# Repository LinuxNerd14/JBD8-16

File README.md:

# The JBD8-16

A computer with the skeleton of the BE6502 by the revered [Ben Eater](https://eater.net/) with the ultimate goal of running DOOM and making a decent platform for programing in asembly or C at a very fundemental level.

    This computer is currently still deep in hardware development but has a diverse set of planned features like hardware based random numbers and way more RAM than what is reasonable along with an implimentation of the VERA by the [8BitGuy](https://www.the8bitguy.com/).

This is by far not a finished project as these features awaiting implimentation:

1. Memory bank
2. Proper random number generator
3. Micro SD card
4. Better display or VGA output
5. Easily reproducable PCB's

List of contributers:

1. [Brian Dean Ullery](https://github.com/NonzeroCornet)

2. [Joshua Lin Yuan]([LinuxNerd14 (Joshua Yuan) · GitHub](https://github.com/LinuxNerd14))

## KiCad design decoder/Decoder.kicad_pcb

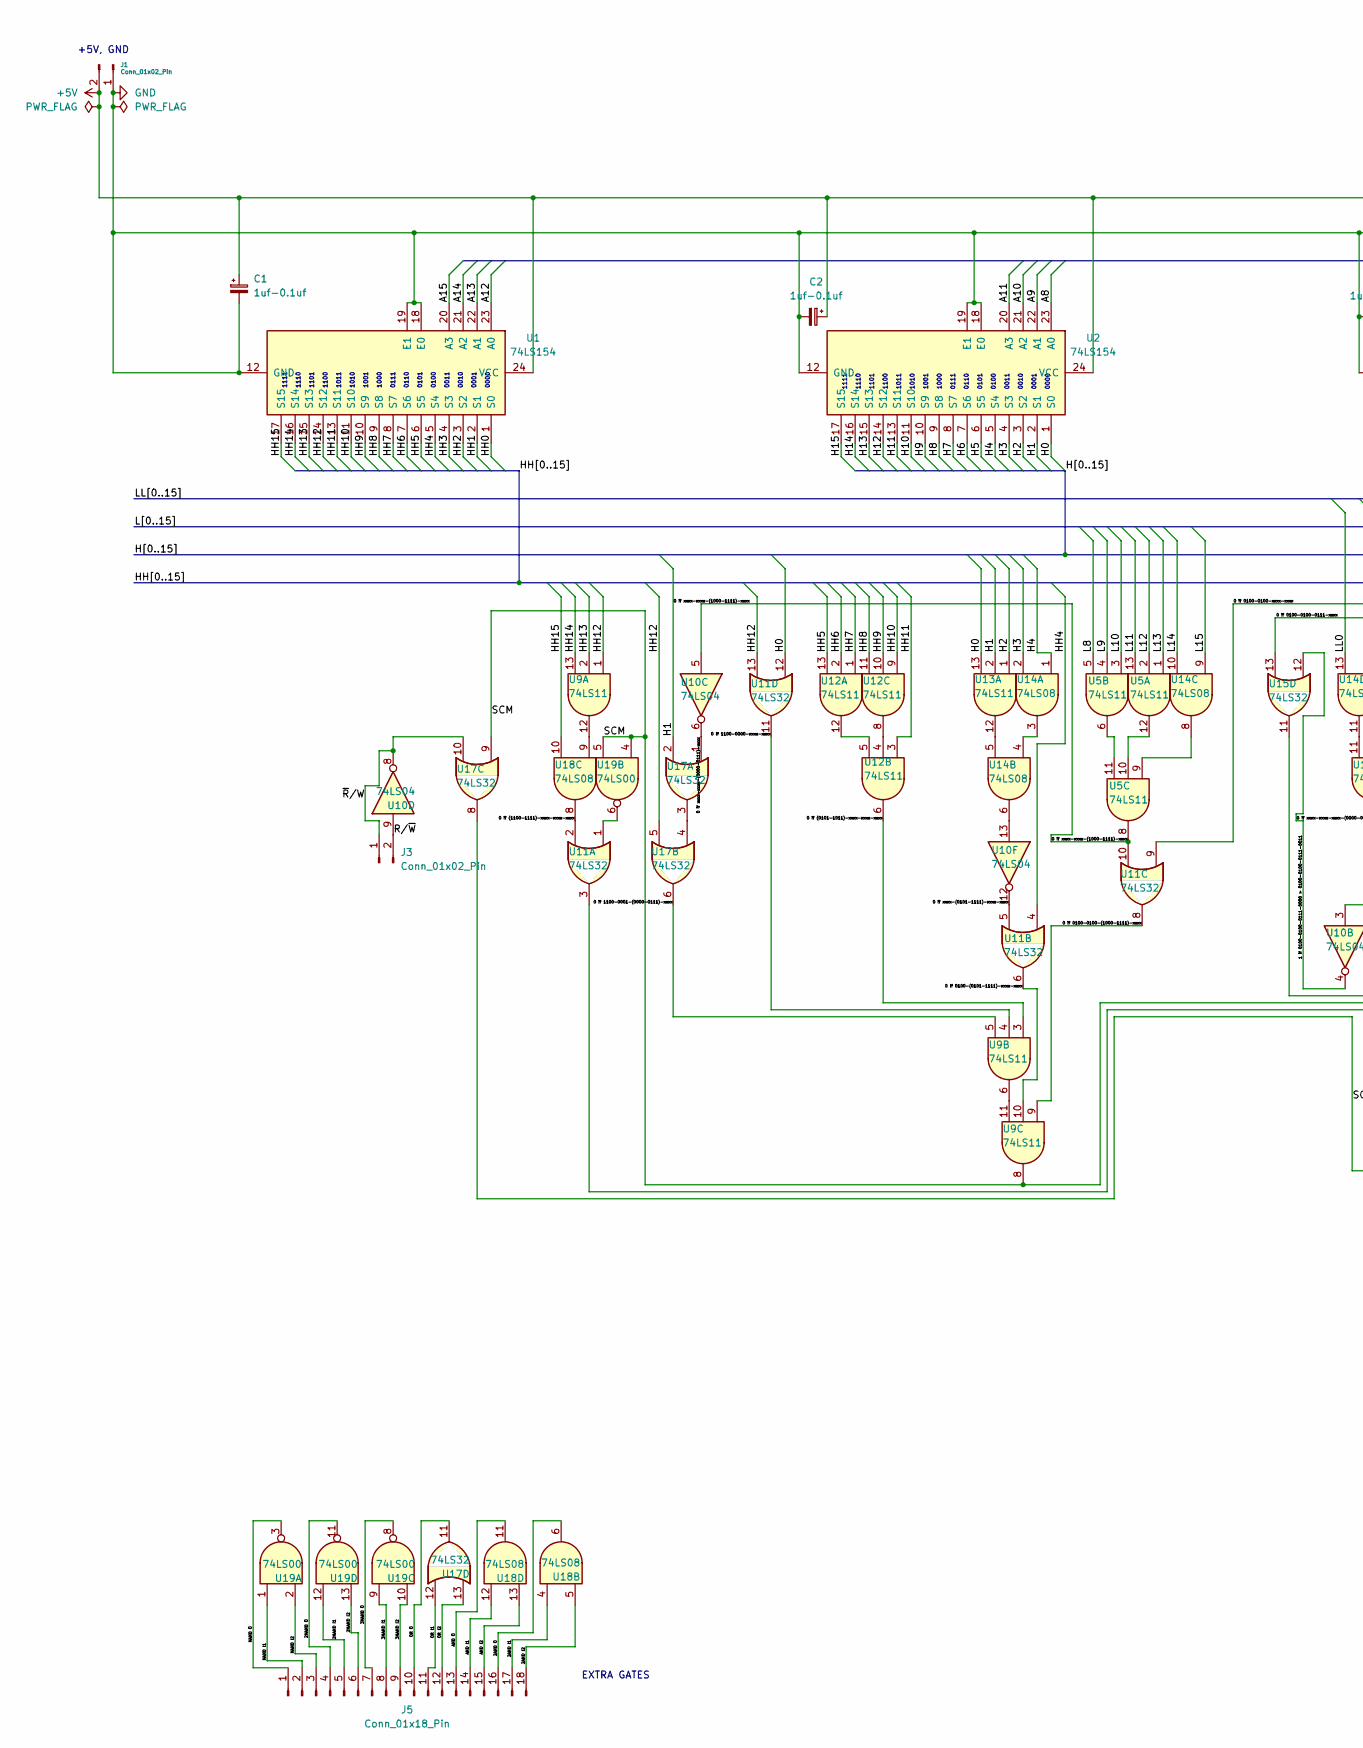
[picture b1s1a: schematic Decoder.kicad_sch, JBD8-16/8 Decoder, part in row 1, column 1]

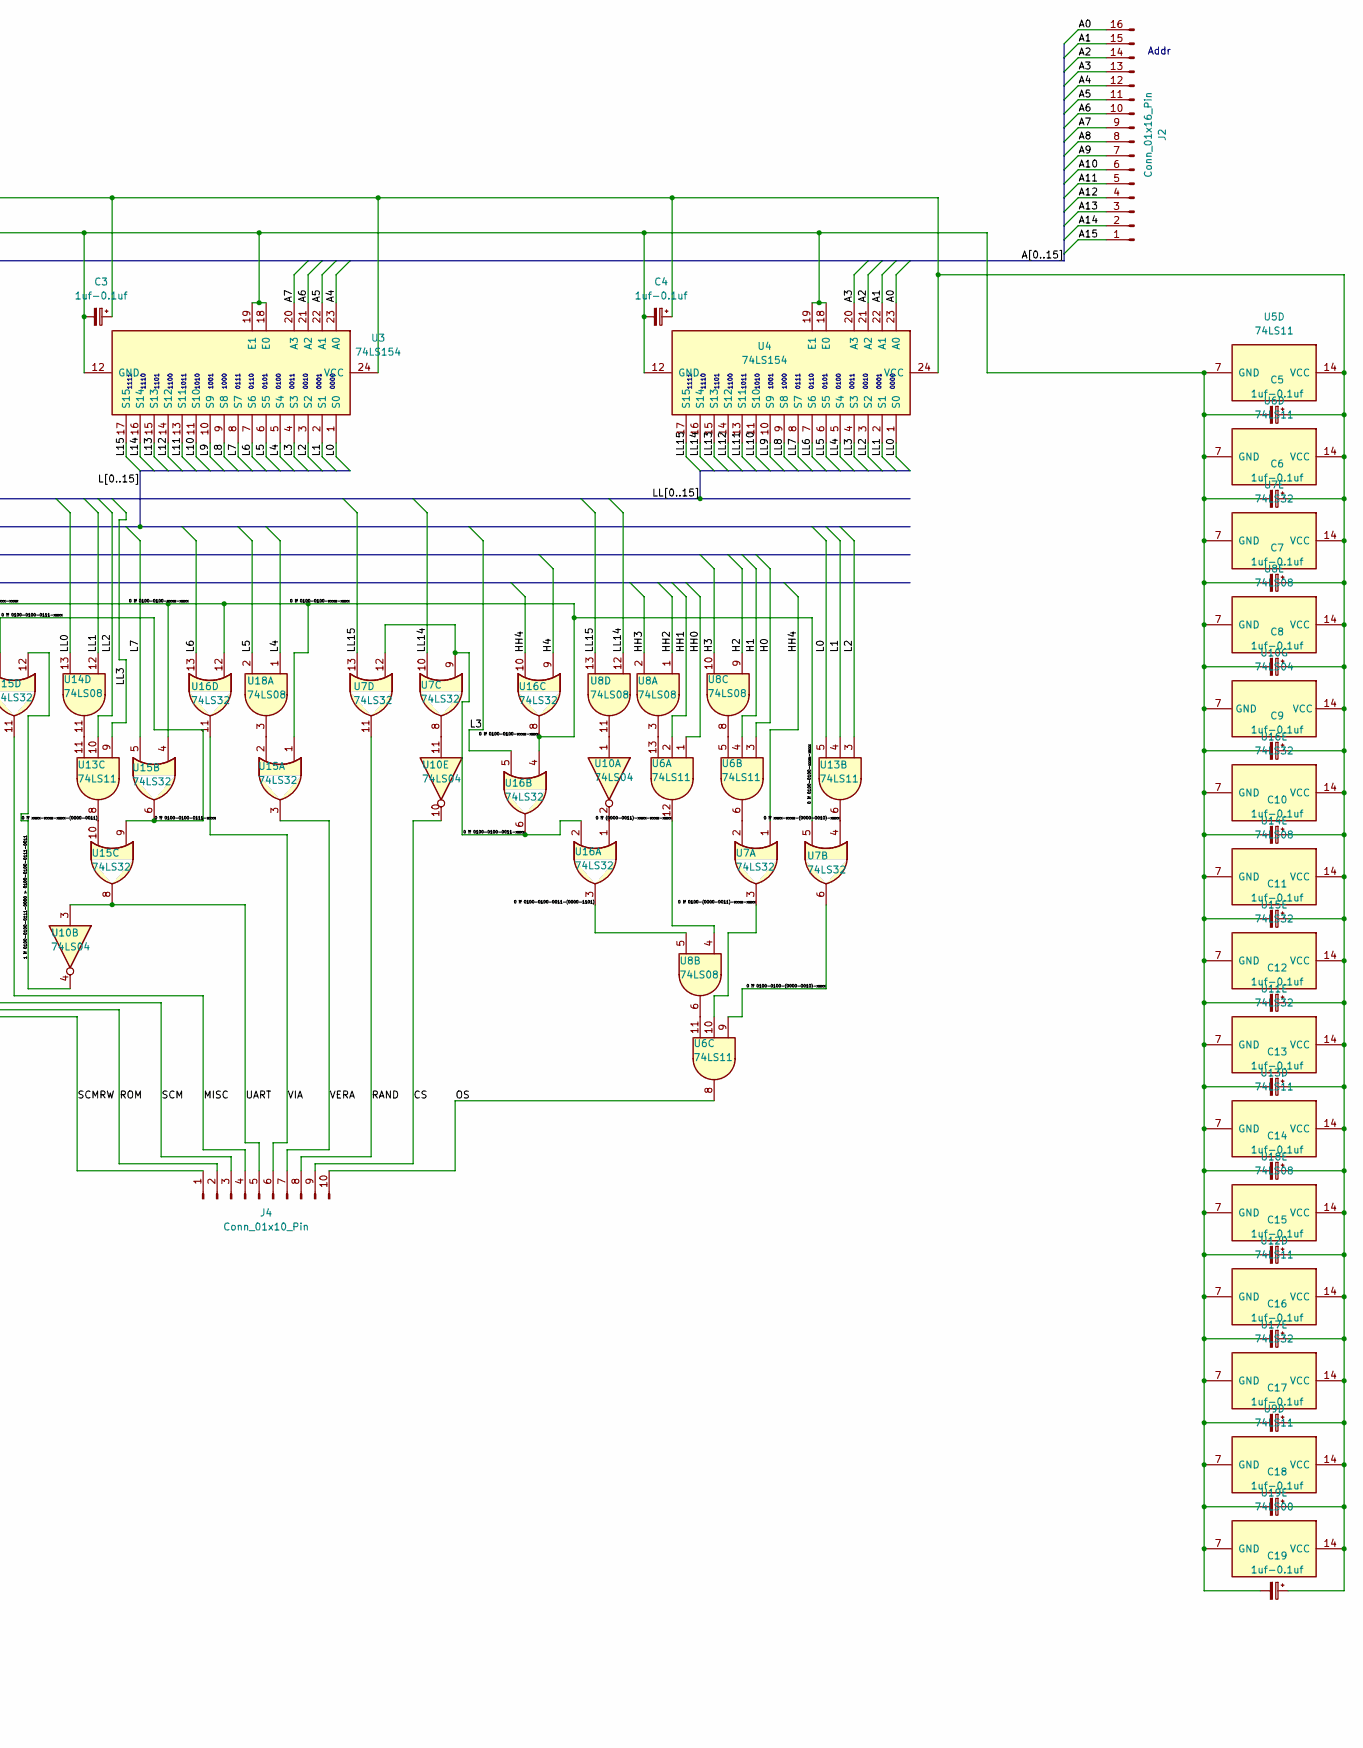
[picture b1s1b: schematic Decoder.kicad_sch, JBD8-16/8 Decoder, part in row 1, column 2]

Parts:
C1, C2, C3, C4, C5, C6, C7, C8, C9, C10, C11, C12, C13, C14, C15, C16, C17, C18, C19: 1uf-0.1uf; CP_Radial_Tantal_D5.0mm_P2.50mm
J1, J3: Conn_01x02_Pin; PinHeader_1x02_P2.54mm_Vertical
J2: Conn_01x16_Pin; PinHeader_1x16_P2.54mm_Vertical
J4: Conn_01x10_Pin; PinHeader_1x10_P2.54mm_Vertical
J5: Conn_01x18_Pin; PinHeader_1x18_P2.54mm_Vertical
U1, U2, U3, U4: 74LS154; DIP-24_W7.62mm_Socket
U5, U6, U9, U12, U13: 74LS11; DIP-14_W7.62mm_Socket
U7, U11, U15, U16, U17: 74LS32; DIP-14_W7.62mm_Socket
U8, U14, U18: 74LS08; DIP-14_W7.62mm_Socket
U10: 74LS04; DIP-14_W7.62mm_Socket
U19: 74LS00; DIP-14_W7.62mm_Socket

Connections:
+5V: C1.1, C2.1, C3.1, C4.1, C5.1, C6.1, C7.1, C8.1, C9.1, C10.1, C11.1, C12.1, C13.1, C14.1, C15.1, C16.1, C17.1, C18.1, C19.1, J1.2, U1.24 (VCC), U2.24 (VCC), U3.24 (VCC), U4.24 (VCC), U5.14 (VCC), U6.14 (VCC), U7.14 (VCC), U8.14 (VCC), U9.14 (VCC), U10.14 (VCC), U11.14 (VCC), U12.14 (VCC), U13.14 (VCC), U14.14 (VCC), U15.14 (VCC), U16.14 (VCC), U17.14 (VCC), U18.14 (VCC), U19.14 (VCC)
/0 if 0100-0100-0011-(0000-1101): U8.5, U16.3
/0 if 0100-0100-0011-xxxx: U7.9, U7.12, U16.2, U16.6
/0 if 0100-0100-0111-xxxx: U15.6, U15.9, U15.13
/0 if 0100-0100-(0000-0010)-xxxx: U6.9, U7.6
/0 if 0100-0100-(1000-1111)-xxxx: U9.9, U11.8
/0 if 0100-0100-xxxx-xxxx: U7.5, U11.9, U15.1, U15.4, U16.4, U16.8, U16.12
/0 if 0100-(0000-0011)-xxxx-xxxx: U6.10, U7.3
/0 if 0100-(0101-1111)-xxxx-xxxx: U9.10, U11.6
/0 if 1100-0000-xxxx-xxxx: U9.4, U11.11
/0 if 1100-0001-(0000-0111)-xxxx: U9.5, U17.6
/0 if (0000-0011)-xxxx-xxxx-xxxx: U6.12, U8.4
/0 if (0101-1011)-xxxx-xxxx-xxxx: U9.3, U12.6
/0 if (1100-1111)-xxxx-xxxx-xxxx: U11.2, U18.8
/0 if xxxx-(0101-1111)-xxxx-xxxx: U10.12, U11.5
/0 if xxxx-xxxx-(0000-0010)-xxxx: U7.4, U13.6
/0 if xxxx-xxxx-(0000-0111)-xxxx: U10.6, U17.1
/0 if xxxx-xxxx-(1000-1111)-xxxx: U5.8, U10.5, U11.10
/0 if xxxx-xxxx-xxxx-(0000-0011): U13.8, U15.10
/1 if 0100-0100-0111-0000 > 0100-0100-0111-0011: U10.4, U15.12
/2AND I1: J5.17, U18.4
/2AND I2: J5.18, U18.5
/2AND O: J5.16, U18.6
/2NAND I1: J5.5, U19.12
/2NAND I2: J5.6, U19.13
/2NAND O: J5.4, U19.11
/3NAND I1: J5.8, U19.9
/3NAND I2: J5.9, U19.10
/3NAND O: J5.7, U19.8
/A0: J2.16, U4.23 (A0)
/A1: J2.15, U4.22 (A1)
/A2: J2.14, U4.21 (A2)
/A3: J2.13, U4.20 (A3)
/A4: J2.12, U3.23 (A0)
/A5: J2.11, U3.22 (A1)
/A6: J2.10, U3.21 (A2)
/A7: J2.9, U3.20 (A3)
/A8: J2.8, U2.23 (A0)
/A9: J2.7, U2.22 (A1)
/A10: J2.6, U2.21 (A2)
/A11: J2.5, U2.20 (A3)
/A12: J2.4, U1.23 (A0)
/A13: J2.3, U1.22 (A1)
/A14: J2.2, U1.21 (A2)
/A15: J2.1, U1.20 (A3)
/AND I1: J5.14, U18.12
/AND I2: J5.15, U18.13
/AND O: J5.13, U18.11
/CS: J4.9, U10.10
/H0: U2.1 (S0), U6.3, U11.12, U13.13
/H1: U2.2 (S1), U6.4, U13.2, U17.2
/H2: U2.3 (S2), U8.9, U13.1
/H3: U2.4 (S3), U8.10, U14.2
/H4: U2.5 (S4), U14.1, U16.9
/H5: U2.6 (S5)
/H6: U2.7 (S6)
/H7: U2.8 (S7)
/H8: U2.9 (S8)
/H9: U2.10 (S9)
/H10: U2.11 (S10)
/H11: U2.13 (S11)
/H12: U2.14 (S12)
/H13: U2.15 (S13)
/H14: U2.16 (S14)
/H15: U2.17 (S15)
/HH0: U1.1 (S0), U6.1
/HH1: U1.2 (S1), U6.2
/HH2: U1.3 (S2), U8.1
/HH3: U1.4 (S3), U8.2
/HH4: U1.5 (S4), U7.1, U11.4, U16.10
/HH5: U1.6 (S5), U12.13
/HH6: U1.7 (S6), U12.2
/HH7: U1.8 (S7), U12.1
/HH8: U1.9 (S8), U12.11
/HH9: U1.10 (S9), U12.10
/HH10: U1.11 (S10), U12.9
/HH11: U1.13 (S11), U12.3
/HH12: U1.14 (S12), U9.1, U11.13, U17.5
/HH13: U1.15 (S13), U9.2
/HH14: U1.16 (S14), U9.13
/HH15: U1.17 (S15), U18.10
/L0: U3.1 (S0), U13.5
/L1: U3.2 (S1), U13.4
/L2: U3.3 (S2), U13.3
/L3: U3.4 (S3), U16.5
/L4: U3.5 (S4), U18.1
/L5: U3.6 (S5), U18.2
/L6: U3.7 (S6), U16.13
/L7: U3.8 (S7), U15.5
/L8: U3.9 (S8), U5.5
/L9: U3.10 (S9), U5.4
/L10: U3.11 (S10), U5.3
/L11: U3.13 (S11), U5.13
/L12: U3.14 (S12), U5.2
/L13: U3.15 (S13), U5.1
/L14: U3.16 (S14), U14.10
/L15: U3.17 (S15), U14.9
/LL0: U4.1 (S0), U14.13
/LL1: U4.2 (S1), U14.12
/LL2: U4.3 (S2), U13.10
/LL3: U4.4 (S3), U13.9
/LL4: U4.5 (S4)
/LL5: U4.6 (S5)
/LL6: U4.7 (S6)
/LL7: U4.8 (S7)
/LL8: U4.9 (S8)
/LL9: U4.10 (S9)
/LL10: U4.11 (S10)
/LL11: U4.13 (S11)
/LL12: U4.14 (S12)
/LL13: U4.15 (S13)
/LL14: U4.16 (S14), U7.10, U8.12
/LL15: U4.17 (S15), U7.13, U8.13
/MISC: J4.4, U15.11
/NAND I1: J5.2, U19.1
/NAND I2: J5.3, U19.2
/NAND O: J5.1, U19.3
/OR I1: J5.11, U17.12
/OR I2: J5.12, U17.13
/OR O: J5.10, U17.11
/OS: J4.10, U6.8
/RAND: J4.8, U7.11
/ROM: J4.2, U11.3
/R/~W: J3.2, U10.9
/SCM: J4.3, U9.8, U17.9, U19.4, U19.5
/SCMRW: J4.1, U17.8
/UART: J4.5, U10.3, U15.8
/VERA: J4.7, U15.3
/VIA: J4.6, U16.11
/~R/W: J3.1, U10.8, U17.10
GND: C1.2, C2.2, C3.2, C4.2, C5.2, C6.2, C7.2, C8.2, C9.2, C10.2, C11.2, C12.2, C13.2, C14.2, C15.2, C16.2, C17.2, C18.2, C19.2, J1.1, U1.12 (GND), U1.18 (E0), U1.19 (E1), U2.12 (GND), U2.18 (E0), U2.19 (E1), U3.12 (GND), U3.18 (E0), U3.19 (E1), U4.12 (GND), U4.18 (E0), U4.19 (E1), U5.7 (GND), U6.7 (GND), U7.7 (GND), U8.7 (GND), U9.7 (GND), U10.7 (GND), U11.7 (GND), U12.7 (GND), U13.7 (GND), U14.7 (GND), U15.7 (GND), U16.7 (GND), U17.7 (GND), U18.7 (GND), U19.7 (GND)
unnamed: U5.10, U5.12
unnamed: U5.6, U5.11
unnamed: U6.5, U8.8
unnamed: U6.6, U7.2
unnamed: U6.11, U8.6
unnamed: U6.13, U8.3
unnamed: U9.6, U9.11
unnamed: U8.11, U10.1
unnamed: U10.2, U16.1
unnamed: U7.8, U10.11
unnamed: U10.13, U14.6
unnamed: U11.1, U19.6
unnamed: U12.4, U12.8
unnamed: U12.5, U12.12
unnamed: U13.11, U14.11
unnamed: U13.12, U14.5
unnamed: U14.3, U14.4
unnamed: U5.9, U14.8
unnamed: U15.2, U18.3
unnamed: U17.3, U17.4
unnamed: U9.12, U18.9

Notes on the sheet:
Addr
EXTRA GATES
1111 1110 1101 1100 1011 1010 1001 1000 0111 0110 0101 0100 0011 0010 0001 0000
+5V, GND

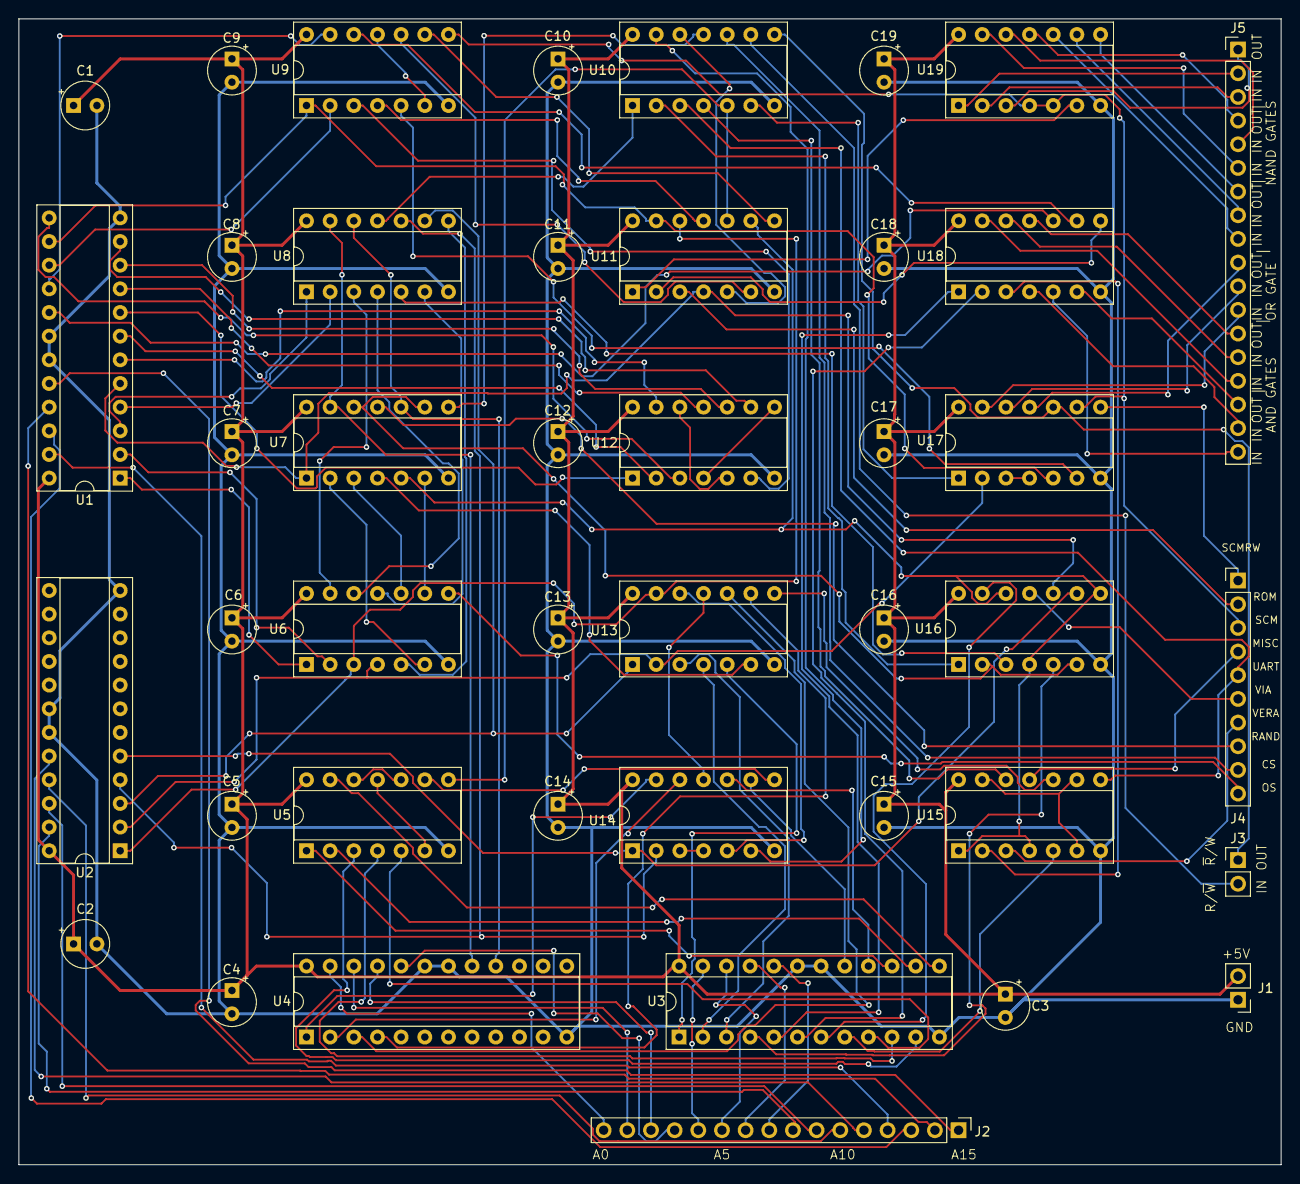
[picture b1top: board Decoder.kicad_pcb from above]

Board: 2 copper layers, 135.5 x 123.0 mm, 43 parts (0 on the bottom side), 131 nets.

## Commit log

2024-10-26 JBD8-16
2024-10-27 worked on SCM
2024-10-28 Better README
2024-11-03 Worked on SCM and README FIX THE GAP IN THE SCM BETWEEN 0000-0110-0001-0000 and 0001-0000-0000-0000
2024-11-03 Finished SCM and made the chematic paper larger
2024-11-04 Worked on OS mem space, adding of 4th decoder needed
2024-11-05 added and image to the README
2024-11-06 Almost done with OS mem and reduced the complexity of many sectors uisng another decoder
2024-11-06 Worked on OS mem
2024-11-06 almost done with ROM and SHM map
2024-11-07 FINISHED MEMORY LOGICgit add .git add .!
2024-11-07 Worked on the BANK
2024-11-08 worked on mem bank
2024-11-08 Made the Mem Bank work properly
2024-11-08 worked on the CS on some chips
2024-11-16 New memory map, New logic, Added VIA, Hooked up a screen and UART, Better memory map table
2024-11-16 updated READMER
2024-11-16 Fixed untracked symbols
2024-11-16 Fixed even more untracked parts
2024-11-23 Fixed unconnected VCC on U24
2024-11-24 general fixes to decoder
2024-11-27 Fixed the decoders being inactive
2024-11-27 Many issues with map which have been labeled
2024-11-27 Removed unneccasary logic
2024-11-27 Made the physiocal layout of the decoder less stupid
2024-11-28 THE DECODER WORKSgit add .
2024-11-30 IT FRICKING WORKS
2024-11-30 added inportant info to text file
2024-12-03 Little bits of optimasition in decoder layout
2025-02-03 Made the BinMemTables.txt more readable
2025-02-03 backaups deleted
2025-02-17 updated image
2025-02-18 added images from osciliscope for reference later
2025-02-23 Memory rearangermations
2025-02-23 removed parts that are on another pcb
2025-02-24 Fixed photo and updated notes
2025-02-25 updates notes from decoder
2025-02-26 Updated Notes based on the notes from the decoder
2025-03-14 updated notes in csonsitency with decoder repo
2025-03-17 spring break
2025-08-30 Merged all repos asociated with the project
2025-09-23 Kicad Backups
2025-09-23 Modified the Location of some docs and added documentation to SerialPortRoutine.asm
2025-09-23 Trying to make a ca65 config for the computer memory map along with transfering the SerialPortRoutine.asm code to work with it
2025-09-30 Finalized converting the SerialPortRoutine.asm from VASM to ca65
2025-09-30 Spring Cleaning
2025-09-30 Even more organization and cleaning
2025-10-01 Started Master doc
2025-10-02 more documentation milarky
2025-10-02 docs
2025-10-04 added to docs and fixed the pad.sh in v1.1 code
2025-10-07 made the LCDtest a loop for endurance testing of the computer
2025-10-07 added to docs
